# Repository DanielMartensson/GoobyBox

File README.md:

# GoobyBox

This project is `GoobyBox`. It's an IO-shield for Arduino UNO. 
The purpose with this project is to provide a simple solution for controlling:

 * 4 x Analog 0-10V inputs
 * 3 x PWM current 0-2A
 * 3 x Digital output current 0-2A
 * 6 x Digital input 24V protection
 * 12/24 voltage supply
 * I2C connection for LCD

This project contains two projects - Surface Mounted Technology(SMT) and Through Hole Technology Mounting (THT).

Software being used: KiCAD 6

This is soldered according to class 3 in the soldering and assembly standard IPC J-STD-001.

Notice that I'm using a `EBC`-transistor here instead of `CBE`-transistor for the analog output.

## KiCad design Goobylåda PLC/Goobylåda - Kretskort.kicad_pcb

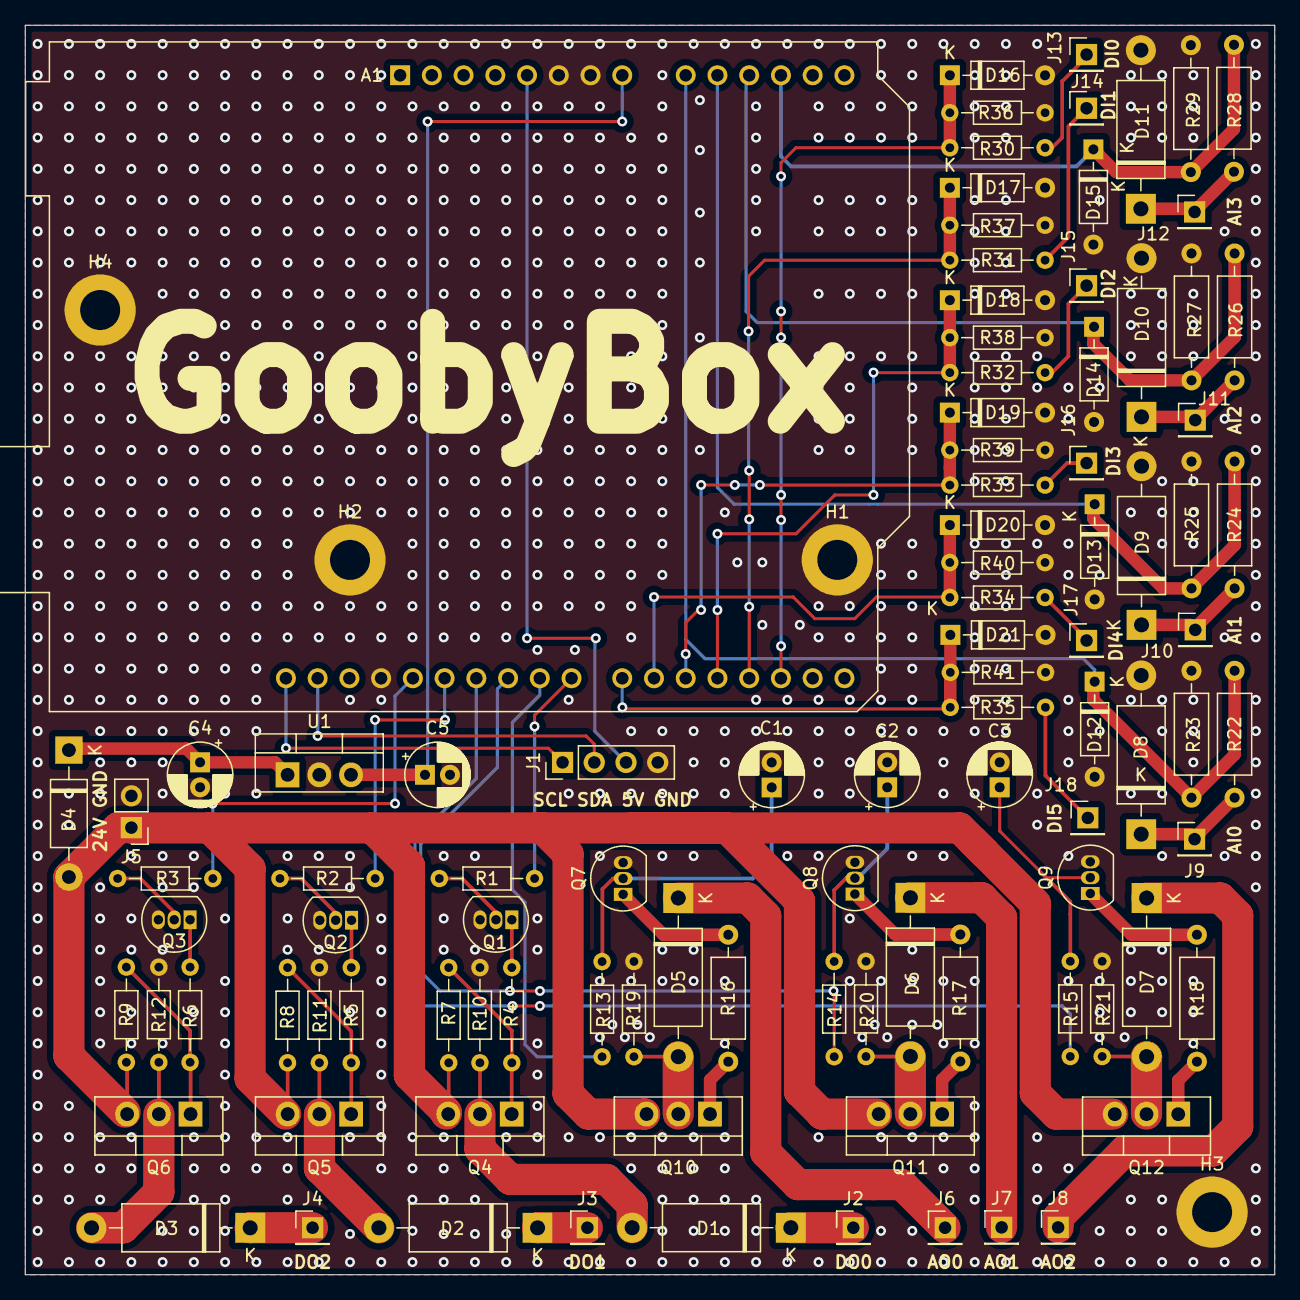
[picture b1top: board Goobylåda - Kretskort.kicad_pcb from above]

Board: 2 copper layers, 100.0 x 100.0 mm, 103 parts (0 on the bottom side), 63 nets.

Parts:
A1: Arduino_UNO_R3
C1, C2, C3: 33uF; CP_Radial_D5.0mm_P2.00mm
C4: 0.33uF; CP_Radial_D5.0mm_P2.00mm
C5: 0.1uF; CP_Radial_D5.0mm_P2.00mm
D1, D2, D3, D5, D6, D7, D8, D9, D10, D11: 1N5400K; D_DO-15_P12.70mm_Horizontal
D4: 600V 1A; D_DO-41_SOD81_P10.16mm_Horizontal
D12, D13, D14, D15, D16, D17, D18, D19, D20, D21: 5.2V; D_DO-35_SOD27_P7.62mm_Horizontal
H1, H2, H3, H4: M3; MountingHole_3.2mm_M3_ISO7380_Pad
J1: LCD 1602 kontakt; PinHeader_1x04_P2.54mm_Vertical
J2, J3, J4, J6, J7, J8, J9, J10, J11, J12, J13, J14, J15, J16, J17, J18: Anslutning; PinHeader_1x01_P2.54mm_Vertical
J5: Anslutning; PinHeader_1x02_P2.54mm_Vertical
Q1, Q2, Q3, Q7, Q8, Q9: 2N2222; TO-92_Inline
Q4, Q5, Q6: IRF9630; TO-220-3_Vertical
Q10, Q11, Q12: MJE29555T; TO-220-3_Vertical
R1, R2, R3, R13, R14, R15: 100; R_Axial_DIN0204_L3.6mm_D1.6mm_P7.62mm_Horizontal
R4, R5, R6, R7, R8, R9, R10, R11, R12, R19, R20, R21, R36, R37, R38, R39, R40, R41: 100k; R_Axial_DIN0204_L3.6mm_D1.6mm_P7.62mm_Horizontal
R16, R17, R18: 1k, 1W; R_Axial_DIN0207_L6.3mm_D2.5mm_P10.16mm_Horizontal
R22, R23, R24, R25, R26, R27, R28, R29: 1k, 250 mW; R_Axial_DIN0207_L6.3mm_D2.5mm_P10.16mm_Horizontal
R30, R31, R32, R33, R34, R35: 10k; R_Axial_DIN0204_L3.6mm_D1.6mm_P7.62mm_Horizontal
U1: LM7812_TO220; TO-220-3_Vertical

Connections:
+5V: A1.5 (+5V), J1.3
+12V: A1.8 (VIN), C5.1, U1.3 (VO)
+24V: D4.2 (A), J5.1, Q4.3 (S), Q5.3 (S), Q6.3 (S), Q10.3 (E), Q11.3 (E), Q12.3 (E), R7.1, R8.1, R9.1
/A0: A1.9 (A0), D12.1 (K), R22.2, R23.1
/A1: A1.10 (A1), D13.1 (K), R24.2, R25.1
/A2: A1.11 (A2), D14.1 (K), R26.2, R27.1
/A3: A1.12 (A3), D15.1 (K), R28.2, R29.1
/AI_0: D8.1 (K), J9.1, R22.1
/AI_1: D9.1 (K), J10.1, R24.1
/AI_2: D10.1 (K), J11.1, R26.1
/AI_3: D11.1 (K), J12.1, R28.1
/AO_0: D5.1 (K), J6.1
/AO_1: D6.1 (K), J7.1
/AO_2: D7.1 (K), J8.1
/D8: A1.23 (D8), R1.2
/D9: A1.24 (D9), R13.2
/D10: A1.25 (D10), R14.2
/D11: A1.26 (D11), R15.2
/D12: A1.27 (D12), R2.2
/D13: A1.28 (D13), R3.2
/DI2: A1.17 (D2), D16.1 (K), R30.1, R36.1
/DI3: A1.18 (D3), D17.1 (K), R31.1, R37.1
/DI4: A1.19 (D4), D18.1 (K), R32.1, R38.1
/DI5: A1.20 (D5), D19.1 (K), R33.1, R39.1
/DI6: A1.21 (D6), D20.1 (K), R34.1, R40.1
/DI7: A1.22 (D7), D21.1 (K), R35.1, R41.1
/DI_0: J13.1, R30.2
/DI_1: J14.1, R31.2
/DI_2: J15.1, R32.2
/DI_3: J16.1, R33.2
/DI_4: J17.1, R34.2
/DI_5: J18.1, R35.2
/DO_0: D1.1 (K), J2.1
/DO_1: D2.1 (K), J3.1
/DO_2: D3.1 (K), J4.1
/SCL: A1.32 (SCL/A5), J1.1
/SDA: A1.31 (SDA/A4), J1.2
GND: A1.6 (GND), A1.7 (GND), A1.29 (GND), C1.2, C2.2, C3.2, C4.2, C5.2, D8.2 (A), D9.2 (A), D10.2 (A), D11.2 (A), D12.2 (A), D13.2 (A), D14.2 (A), D15.2 (A), D16.2 (A), D17.2 (A), D18.2 (A), D19.2 (A), D20.2 (A), D21.2 (A), H1.1, H2.1, H3.1, H4.1, J1.4, J5.2, Q1.3 (E), Q2.3 (E), Q3.3 (E), Q7.3 (E), Q8.3 (E), Q9.3 (E), R10.2, R11.2, R12.2, R19.2, R20.2, R21.2, R23.2, R25.2, R27.2, R29.2, R36.2, R37.2, R38.2, R39.2, R40.2, R41.2, U1.2 (GND)
unnamed: C1.1, Q7.2 (B), R13.1
unnamed: C2.1, Q8.2 (B), R14.1
unnamed: C3.1, Q9.2 (B), R15.1
unnamed: C4.1, D4.1 (K), U1.1 (VI)
unnamed: D1.2 (A), Q4.2 (D), R10.1
unnamed: D2.2 (A), Q5.2 (D), R11.1
unnamed: D3.2 (A), Q6.2 (D), R12.1
unnamed: D5.2 (A), Q10.2 (C), R19.1
unnamed: D6.2 (A), Q11.2 (C), R20.1
unnamed: D7.2 (A), Q12.2 (C), R21.1
unnamed: Q1.1 (C), R4.2
unnamed: Q1.2 (B), R1.1
unnamed: Q2.1 (C), R5.2
unnamed: Q2.2 (B), R2.1
unnamed: Q3.1 (C), R6.2
unnamed: Q3.2 (B), R3.1
unnamed: Q4.1 (G), R4.1, R7.2
unnamed: Q5.1 (G), R5.1, R8.2
unnamed: Q6.1 (G), R6.1, R9.2
unnamed: Q7.1 (C), R16.2
unnamed: Q8.1 (C), R17.2
unnamed: Q9.1 (C), R18.2
unnamed: Q10.1 (B), R16.1
unnamed: Q11.1 (B), R17.1
unnamed: Q12.1 (B), R18.1

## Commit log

2024-01-11 First upload
2024-01-14 Update for THT
2024-01-17 new picture for GoobyBox
2024-01-18 mounting holes
2024-01-19 update schematic
2024-02-15 Update PCB board
2024-02-19 add with Arduino
